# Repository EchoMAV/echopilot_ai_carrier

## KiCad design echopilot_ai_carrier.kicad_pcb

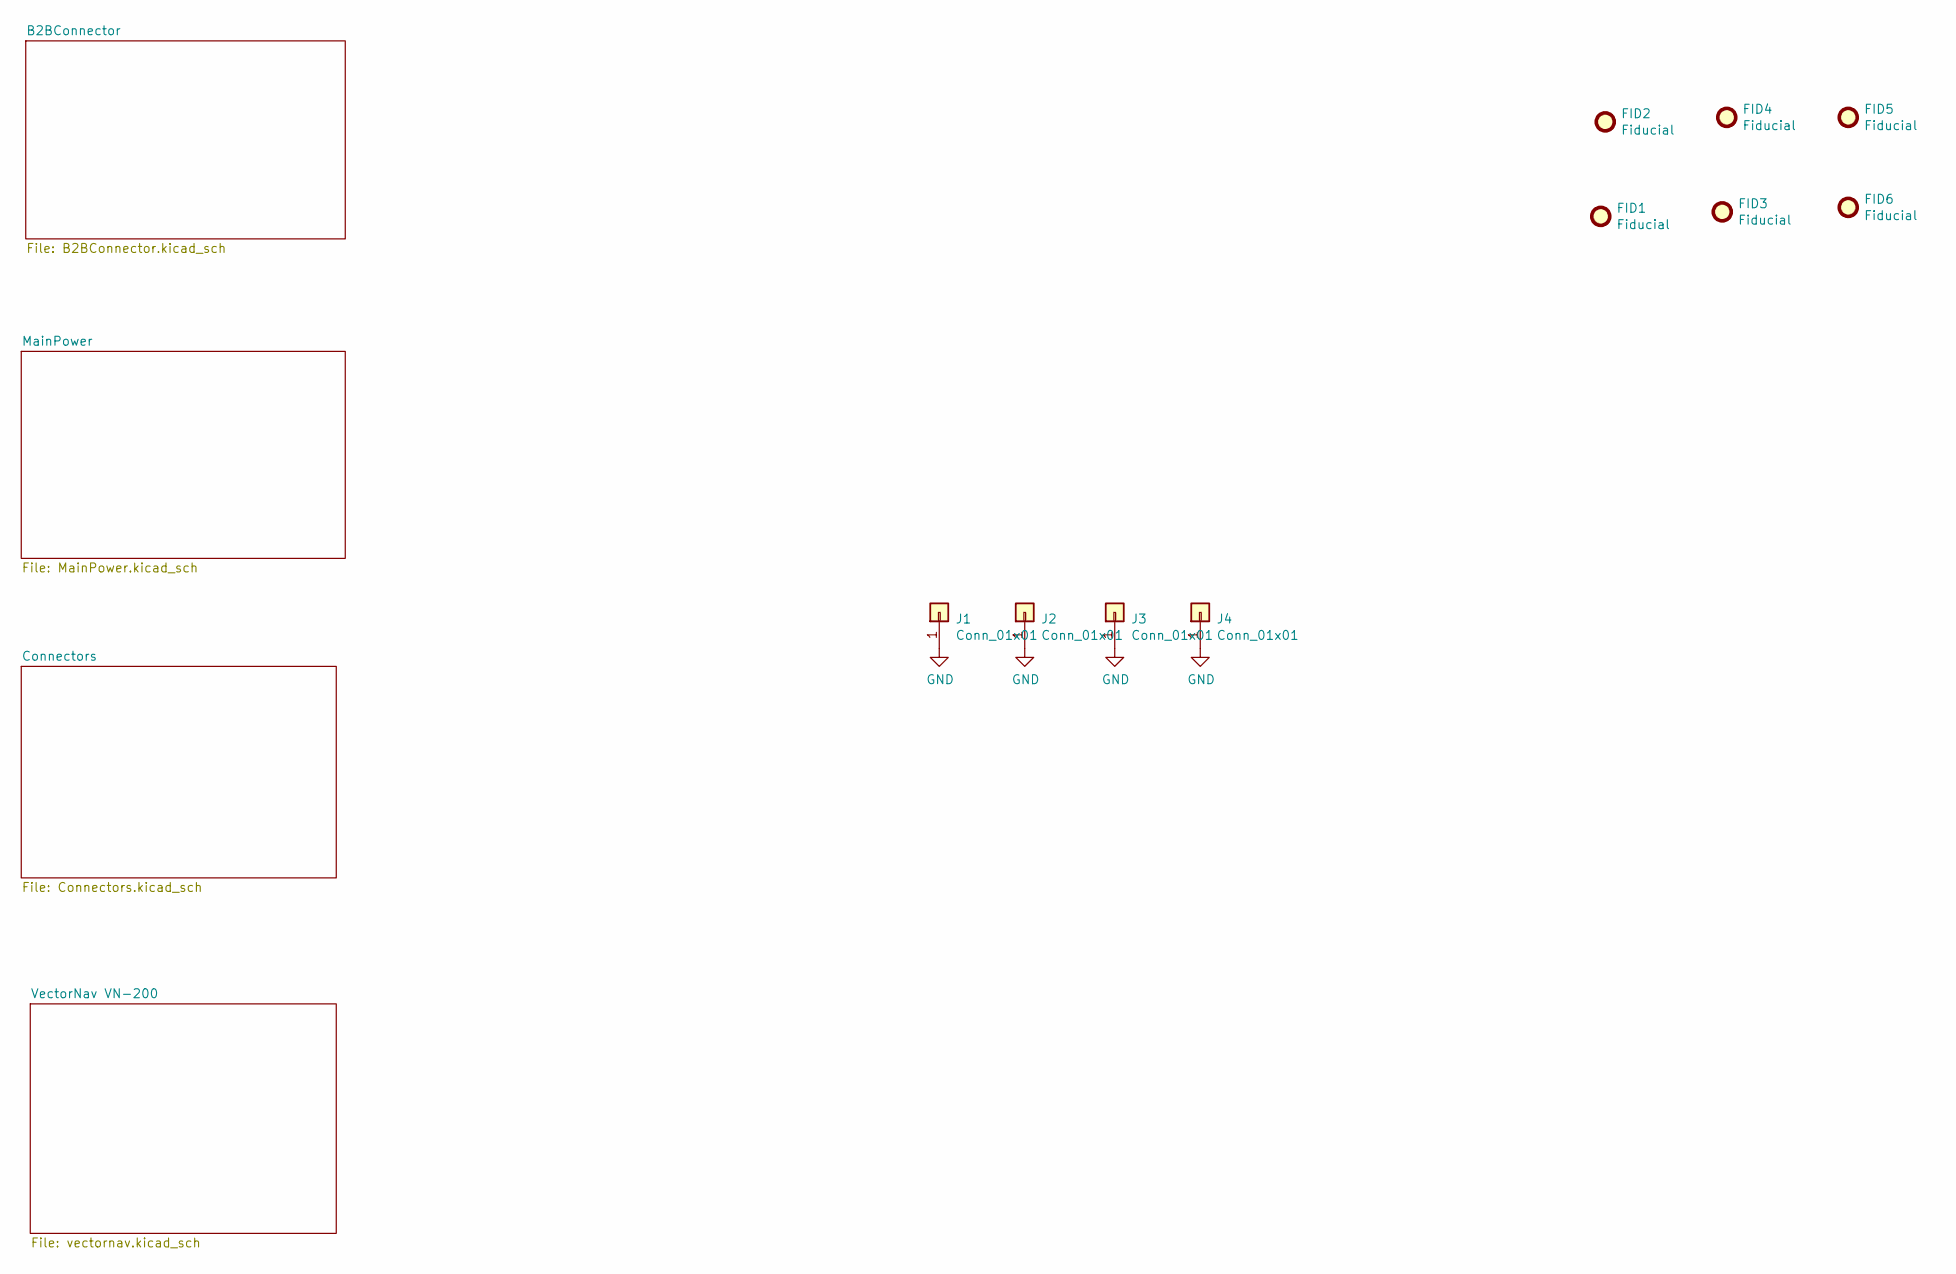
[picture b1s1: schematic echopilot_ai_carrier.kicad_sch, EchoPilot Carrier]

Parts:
FID1, FID2, FID3, FID4, FID5, FID6: Fiducial; Fiducial_0.5mm_Dia_1mm_Outer; Part Num DNI
J1, J2, J3, J4: Conn_01x01; MountingHole_2.7mm_M2.5_Pad_Via; Part Num DNI

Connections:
GND: J1.1, J2.1, J3.1, J4.1; also elsewhere on the board

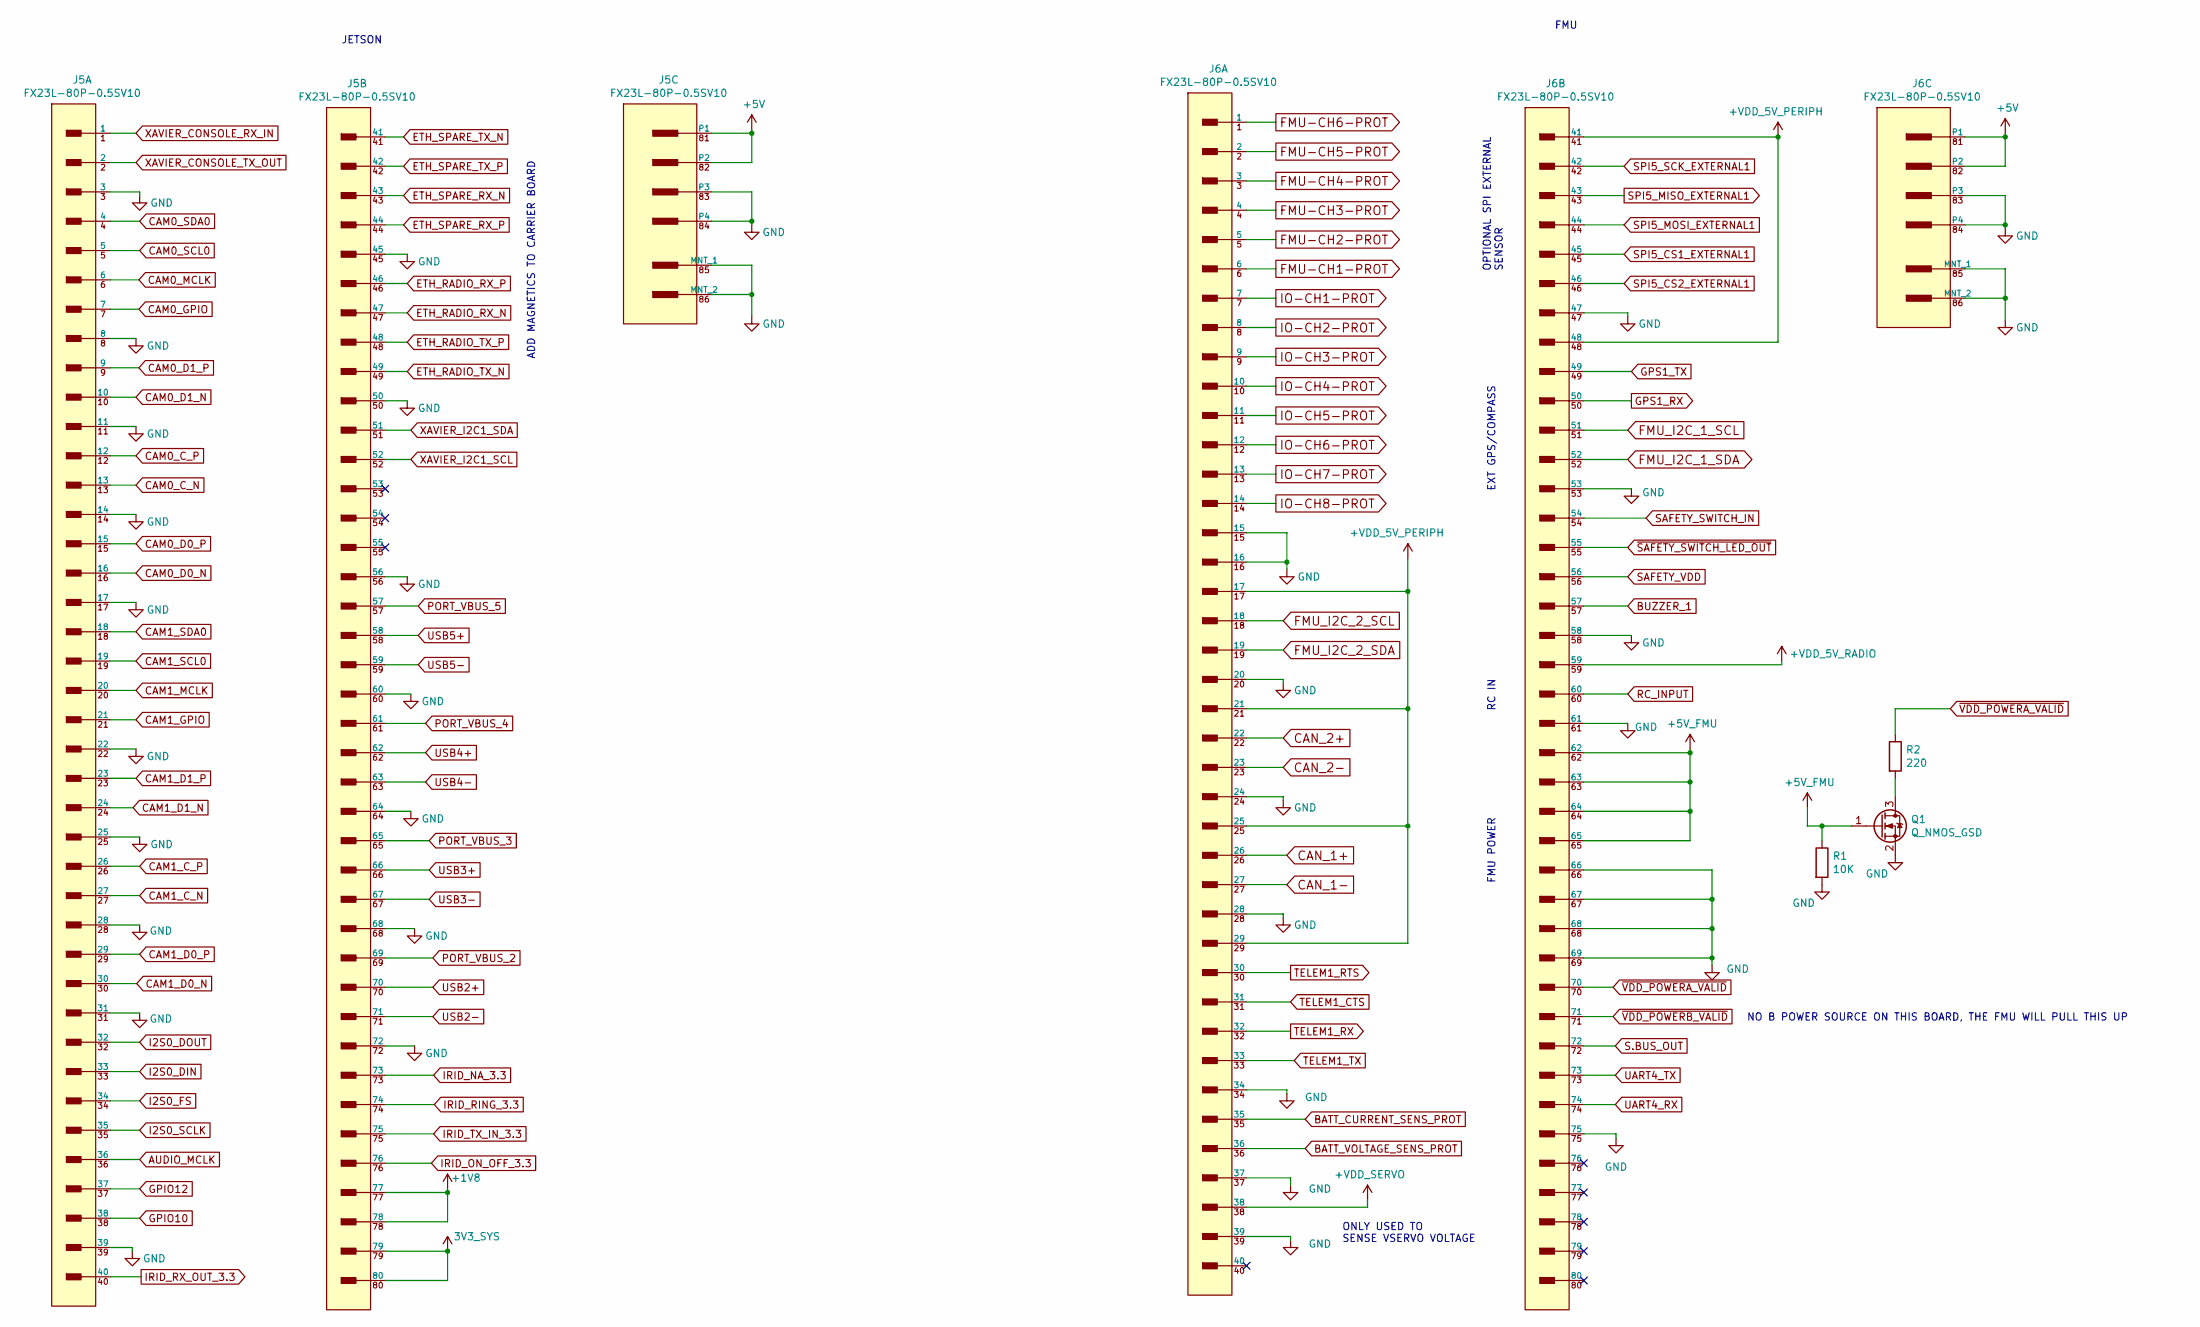
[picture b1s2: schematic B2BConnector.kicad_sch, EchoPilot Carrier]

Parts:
J5: FX23L-80P-0.5SV10; Hirose-FX23L-80P-0.5SV8-MFG; current rating 0.5/3A; voltage rating 50/200V; mouser part number 798-FX23L-80P-0.5SV8; digikey description CONN HDR
J6: FX23L-80P-0.5SV10; Hirose-FX23L-80P-0.5SV8-MFG; current rating 0.5/3A; voltage rating 50/200V; mouser part number FX23L-80P-0.5SV10; digikey description CONN HDR
Q1: Q_NMOS_GSD; SOT-23; Part Num BSS214NH6327XTSA1
R1: 10K; R_0201_0603Metric; Part Num ERJ-1GNF1002C
R2: 220; R_0201_0603Metric; Part Num ERJ-1GNF2200C

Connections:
3V3_SYS: J5.79, J5.80; also elsewhere on the board
+1V8: J5.77, J5.78
+5V_FMU: J6.62, J6.63, J6.64, J6.65, Q1.1 (G), R1.1; also elsewhere on the board
+VDD_5V_PERIPH: J6.17, J6.21, J6.25, J6.29, J6.41, J6.48; also elsewhere on the board
+VDD_5V_RADIO: J6.59; also elsewhere on the board
+VDD_SERVO: J6.38; also elsewhere on the board
AUDIO_MCLK: J5.36
BATT_CURRENT_SENS_PROT: J6.35; also elsewhere on the board
BATT_VOLTAGE_SENS_PROT: J6.36; also elsewhere on the board
BUZZER_1: J6.57; also elsewhere on the board
CAM0_C_N: J5.13; also elsewhere on the board
CAM0_C_P: J5.12; also elsewhere on the board
CAM0_D0_N: J5.16; also elsewhere on the board
CAM0_D0_P: J5.15; also elsewhere on the board
CAM0_D1_N: J5.10; also elsewhere on the board
CAM0_D1_P: J5.9; also elsewhere on the board
CAM0_GPIO: J5.7; also elsewhere on the board
CAM0_MCLK: J5.6; also elsewhere on the board
CAM0_SCL0: J5.5; also elsewhere on the board
CAM0_SDA0: J5.4; also elsewhere on the board
CAM1_C_N: J5.27; also elsewhere on the board
CAM1_C_P: J5.26; also elsewhere on the board
CAM1_D0_N: J5.30; also elsewhere on the board
CAM1_D0_P: J5.29; also elsewhere on the board
CAM1_D1_N: J5.24; also elsewhere on the board
CAM1_D1_P: J5.23; also elsewhere on the board
CAM1_GPIO: J5.21; also elsewhere on the board
CAM1_MCLK: J5.20; also elsewhere on the board
CAM1_SCL0: J5.19; also elsewhere on the board
CAM1_SDA0: J5.18; also elsewhere on the board
CAN_1+: J6.26; also elsewhere on the board
CAN_1-: J6.27; also elsewhere on the board
CAN_2+: J6.22; also elsewhere on the board
CAN_2-: J6.23; also elsewhere on the board
ETH_RADIO_RX_N: J5.47; also elsewhere on the board
ETH_RADIO_RX_P: J5.46; also elsewhere on the board
ETH_RADIO_TX_N: J5.49; also elsewhere on the board
ETH_RADIO_TX_P: J5.48; also elsewhere on the board
ETH_SPARE_RX_N: J5.43; also elsewhere on the board
ETH_SPARE_RX_P: J5.44; also elsewhere on the board
ETH_SPARE_TX_N: J5.41; also elsewhere on the board
ETH_SPARE_TX_P: J5.42; also elsewhere on the board
FMU-CH1-PROT: J6.6; also elsewhere on the board
FMU-CH2-PROT: J6.5; also elsewhere on the board
FMU-CH3-PROT: J6.4; also elsewhere on the board
FMU-CH4-PROT: J6.3; also elsewhere on the board
FMU-CH5-PROT: J6.2
FMU-CH6-PROT: J6.1
FMU_I2C_1_SCL: J6.51; also elsewhere on the board
FMU_I2C_1_SDA: J6.52; also elsewhere on the board
FMU_I2C_2_SCL: J6.18; also elsewhere on the board
FMU_I2C_2_SDA: J6.19; also elsewhere on the board
GND: J5.3, J5.8, J5.11, J5.14, J5.17, J5.22, J5.25, J5.28, J5.31, J5.39, J5.45, J5.50, J5.56, J5.60, J5.64, J5.68, J5.72, J5.83 (P3), J5.84 (P4), J5.85 (MNT_1), J5.86 (MNT_2), J6.15, J6.16, J6.20, J6.24, J6.28, J6.34, J6.37, J6.39, J6.47, J6.53, J6.58, J6.61, J6.66, J6.67, J6.68, J6.69, J6.75, J6.83 (P3), J6.84 (P4), J6.85 (MNT_1), J6.86 (MNT_2), Q1.2 (S), R1.2; also elsewhere on the board
GPIO10: J5.38
GPIO12: J5.37
GPS1_RX: J6.50; also elsewhere on the board
GPS1_TX: J6.49; also elsewhere on the board
I2S0_DIN: J5.33
I2S0_DOUT: J5.32
I2S0_FS: J5.34
I2S0_SCLK: J5.35
IO-CH1-PROT: J6.7; also elsewhere on the board
IO-CH2-PROT: J6.8; also elsewhere on the board
IO-CH3-PROT: J6.9; also elsewhere on the board
IO-CH4-PROT: J6.10; also elsewhere on the board
IO-CH5-PROT: J6.11; also elsewhere on the board
IO-CH6-PROT: J6.12; also elsewhere on the board
IO-CH7-PROT: J6.13; also elsewhere on the board
IO-CH8-PROT: J6.14; also elsewhere on the board
IRID_NA_3.3: J5.73; also elsewhere on the board
IRID_ON_OFF_3.3: J5.76; also elsewhere on the board
IRID_RING_3.3: J5.74; also elsewhere on the board
IRID_RX_OUT_3.3: J5.40; also elsewhere on the board
IRID_TX_IN_3.3: J5.75; also elsewhere on the board
unnamed: Q1.3 (D), R2.2
PORT_VBUS_2: J5.69; also elsewhere on the board
PORT_VBUS_3: J5.65; also elsewhere on the board
PORT_VBUS_4: J5.61; also elsewhere on the board
PORT_VBUS_5: J5.57; also elsewhere on the board
RC_INPUT: J6.60; also elsewhere on the board
S.BUS_OUT: J6.72; also elsewhere on the board
SAFETY_SWITCH_IN: J6.54; also elsewhere on the board
SAFETY_VDD: J6.56; also elsewhere on the board
SPI5_CS1_EXTERNAL1: J6.45
SPI5_CS2_EXTERNAL1: J6.46
SPI5_MISO_EXTERNAL1: J6.43
SPI5_MOSI_EXTERNAL1: J6.44
SPI5_SCK_EXTERNAL1: J6.42
TELEM1_CTS: J6.31; also elsewhere on the board
TELEM1_RTS: J6.30; also elsewhere on the board
TELEM1_RX: J6.32; also elsewhere on the board
TELEM1_TX: J6.33; also elsewhere on the board
UART4_RX: J6.74; also elsewhere on the board
UART4_TX: J6.73; also elsewhere on the board
USB2+: J5.70; also elsewhere on the board
USB2-: J5.71; also elsewhere on the board
USB3+: J5.66; also elsewhere on the board
USB3-: J5.67; also elsewhere on the board
USB4+: J5.62; also elsewhere on the board
USB4-: J5.63; also elsewhere on the board
USB5+: J5.58; also elsewhere on the board
USB5-: J5.59; also elsewhere on the board
XAVIER_CONSOLE_RX_IN: J5.1; also elsewhere on the board
XAVIER_CONSOLE_TX_OUT: J5.2; also elsewhere on the board
XAVIER_I2C1_SCL: J5.52
XAVIER_I2C1_SDA: J5.51
~SAFETY_SWITCH_LED_OUT: J6.55; also elsewhere on the board
~VDD_POWERA_VALID: J6.70, R2.1
~VDD_POWERB_VALID: J6.71

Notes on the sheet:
ADD MAGNETICS TO CARRIER BOARD
OPTIONAL SPI EXTERNAL SENSOR
RC IN
NO B POWER SOURCE ON THIS BOARD, THE FMU WILL PULL THIS UP
FMU
FMU POWER
ONLY USED TO SENSE VSERVO VOLTAGE
JETSON
EXT GPS/COMPASS

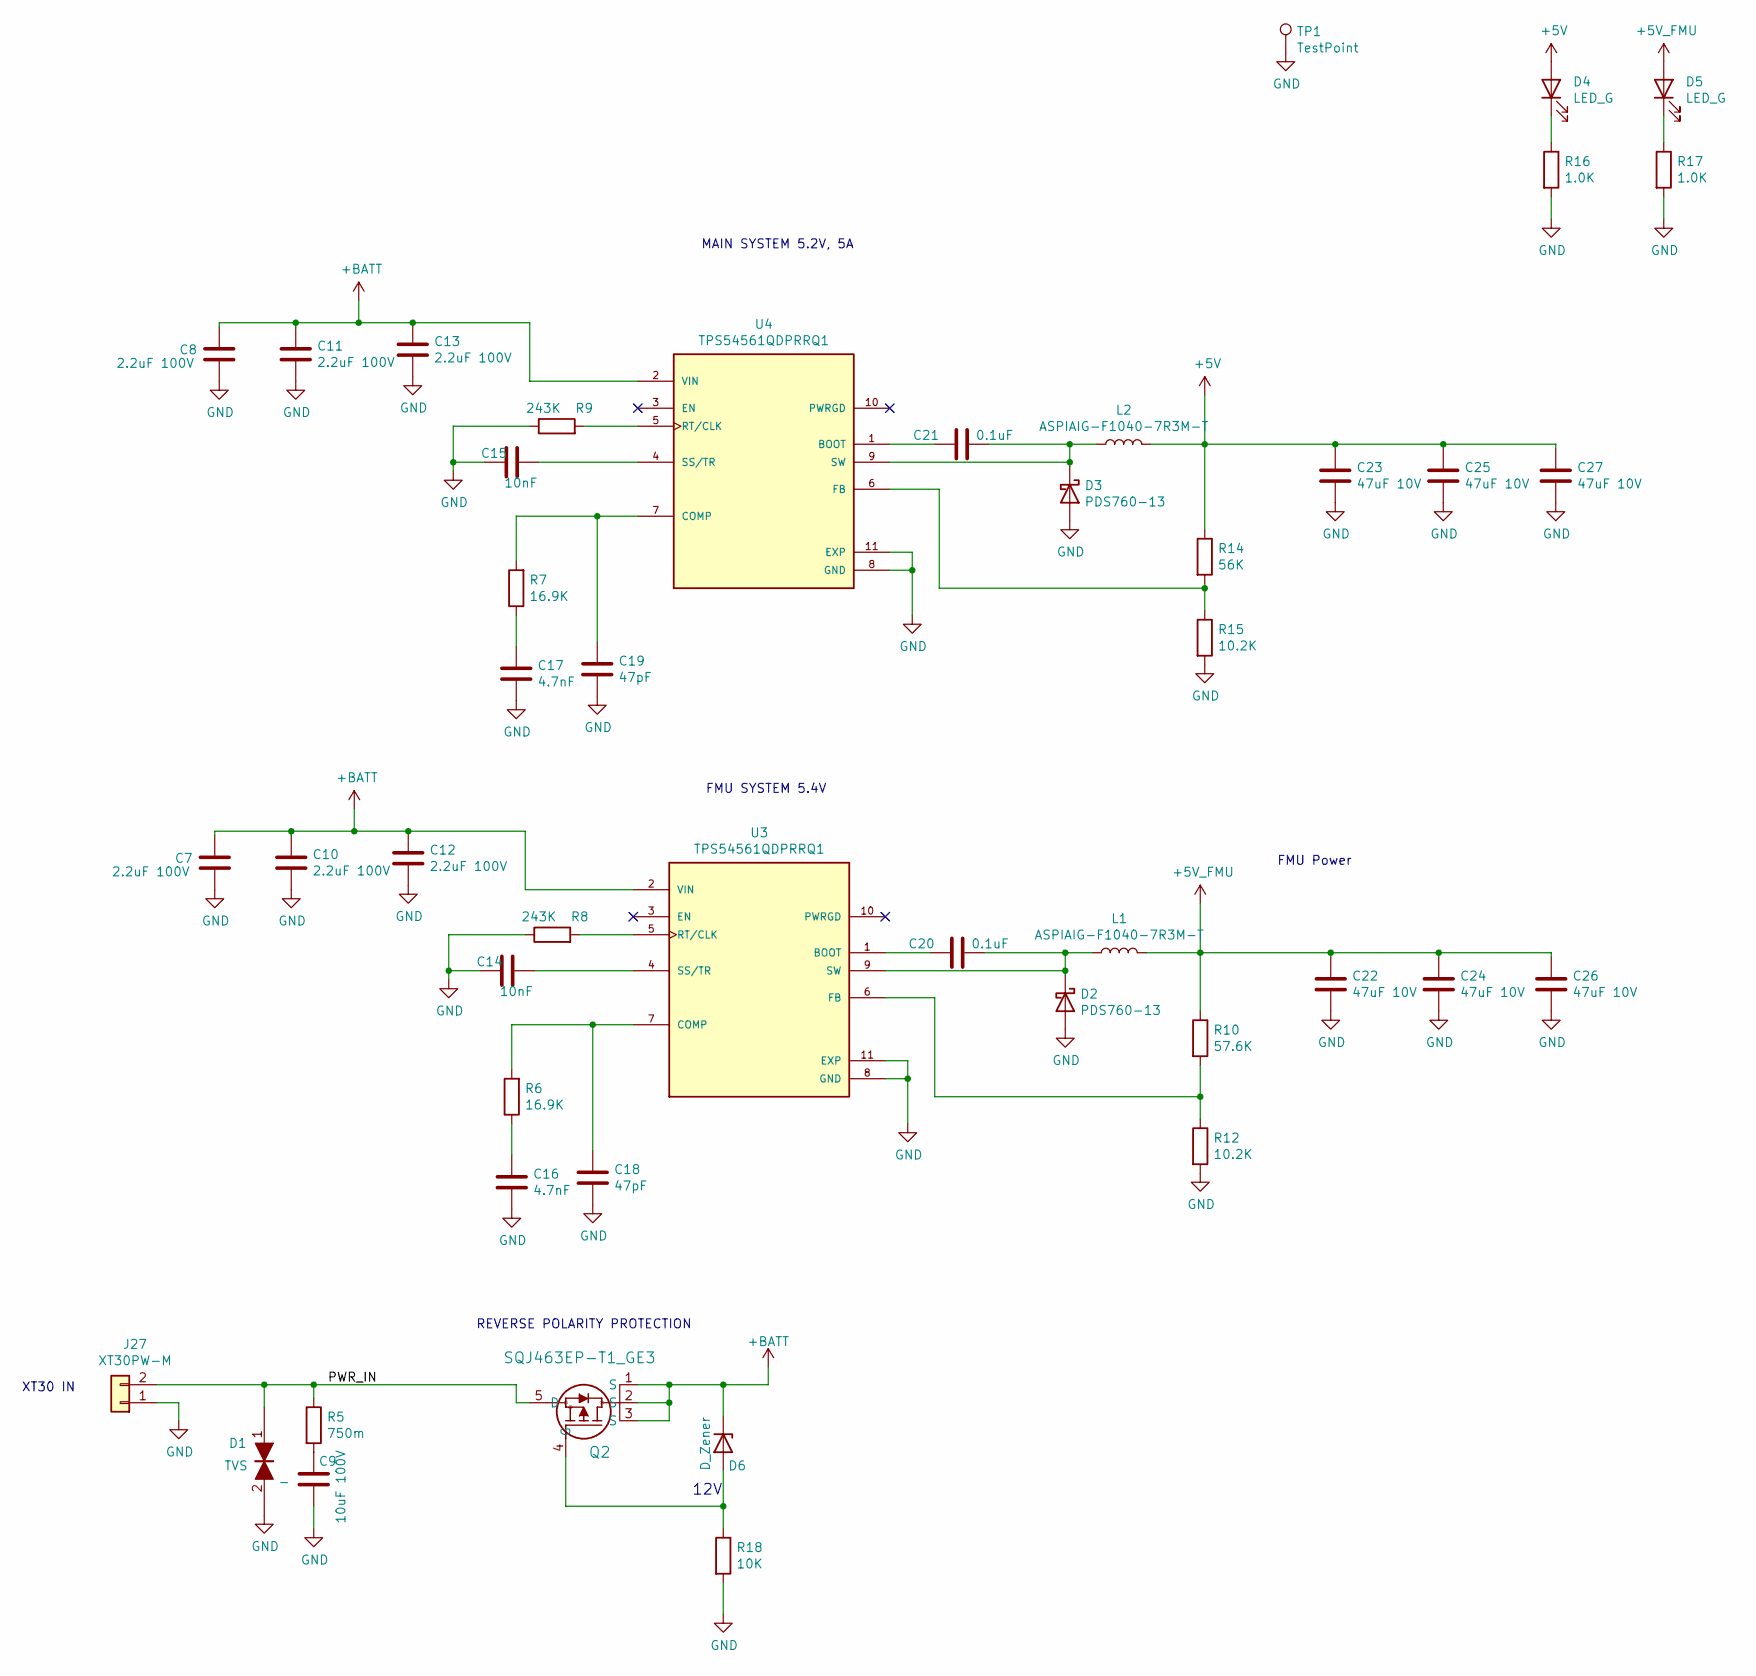
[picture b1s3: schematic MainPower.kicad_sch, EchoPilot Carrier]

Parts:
C7, C8, C10, C11, C12, C13: 2.2uF 100V; C_1206; Part Num 12061C225KAT2A
C9: 10uF 100V; C_1210; Part Num GRM32EC72A106KE05L
C14, C15: 10nF; C_0201; Part Num GRM033R71E103KE14D
C16, C17: 4.7nF; C_0201; Part Num GRM033R61E472KA12D
C18, C19: 47pF; C_0402; Part Num C0402C470J3RACAUTO
C20, C21: 0.1uF; C_0201; Part Num GRM033R61E104KE14J
C22, C23, C24, C25, C26, C27: 47uF 10V; C_1206; Part Num CL31A476MPHNNNE
D1: TVS; D_SOD-123F; Voltage _; Tolerance _; Part Num ATV02W101B-HF
D2, D3: PDS760-13; Part Num PDS760-13
D4, D5: LED_G; LED_0603; Part Num 150060VS75000
D6: D_Zener; D_SOD-523; Part Num MM5Z12VT1G
J27: XT30PW-M; AMASS_XT30PW-M_1x02_P2.50mm_Horizontal; Part Num XT30PW-M
L1, L2: ASPIAIG-F1040-7R3M-T; Part Num ASPIAIG-F1040-7R3M-T
Q2: SQJ463EP-T1_GE3; TO_63EP-T1_GE3_VIS; Part Num SQJ463EP-T1_GE3
R5: 750m; R_0402; Part Num ERJ-2BQJR75X
R6, R7: 16.9K; R_0201_0603Metric; Part Num ERJ-1GNF1692C
R8, R9: 243K; R_0201_0603Metric; Part Num ERJ-1GNF2433C
R10: 57.6K; R_0201_0603Metric; Part Num RC0201FR-0757K6L
R12, R15: 10.2K; R_0201_0603Metric; Part Num ERJ-1GNF1022C
R14: 56K; R_0201_0603Metric; Part Num RC0201FR-0756KL
R16, R17: 1.0K; R_0201_0603Metric; Part Num ERJ-1GEF1001C
R18: 10K; R_0402; Part Num ERJ-PA2J103X
TP1: TestPoint; Test_Point_Keystone_5015_Micro-Minature; Part Num 5015
U3, U4: TPS54561QDPRRQ1; SON80P400X400X80-11N; PARTREV F

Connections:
+5V_FMU: C22.1, C24.1, C26.1, D5.2 (A), L1.2, R10.1; also elsewhere on the board
+BATT: C7.1, C8.1, C10.1, C11.1, C12.1, C13.1, D6.1 (K), Q2.1 (S), Q2.2 (S), Q2.3 (S), U3.2 (VIN), U4.2 (VIN); also elsewhere on the board
/MainPower/PWR_IN: D1.1, J27.2, Q2.5 (D), R5.1
GND: C7.2, C8.2, C9.2, C10.2, C11.2, C12.2, C13.2, C14.2, C15.2, C16.2, C17.2, C18.2, C19.2, C22.2, C23.2, C24.2, C25.2, C26.2, C27.2, D1.2, D2.2 (A), D3.2 (A), J27.1, R8.1, R9.1, R12.2, R15.2, R16.2, R17.2, R18.2, TP1.1, U3.8 (GND), U3.11 (EXP), U4.8 (GND), U4.11 (EXP); also elsewhere on the board
unnamed: C9.1, R5.2
unnamed: C14.1, U3.4 (SS/TR)
unnamed: C15.1, U4.4 (SS/TR)
unnamed: C16.1, R6.1
unnamed: C17.1, R7.1
unnamed: C18.1, R6.2, U3.7 (COMP)
unnamed: C19.1, R7.2, U4.7 (COMP)
unnamed: C20.1, D2.1 (K), L1.1, U3.9 (SW)
unnamed: C20.2, U3.1 (BOOT)
unnamed: C21.1, D3.1 (K), L2.1, U4.9 (SW)
unnamed: C21.2, U4.1 (BOOT)
unnamed: D4.1 (K), R16.1
unnamed: D5.1 (K), R17.1
unnamed: D6.2 (A), Q2.4 (G), R18.1
unnamed: R8.2, U3.5 (RT/CLK)
unnamed: R9.2, U4.5 (RT/CLK)
unnamed: R10.2, R12.1, U3.6 (FB)
unnamed: R14.2, R15.1, U4.6 (FB)

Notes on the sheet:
FMU SYSTEM 5.4V
REVERSE POLARITY PROTECTION
MAIN SYSTEM 5.2V, 5A
12V
XT30 IN
FMU Power

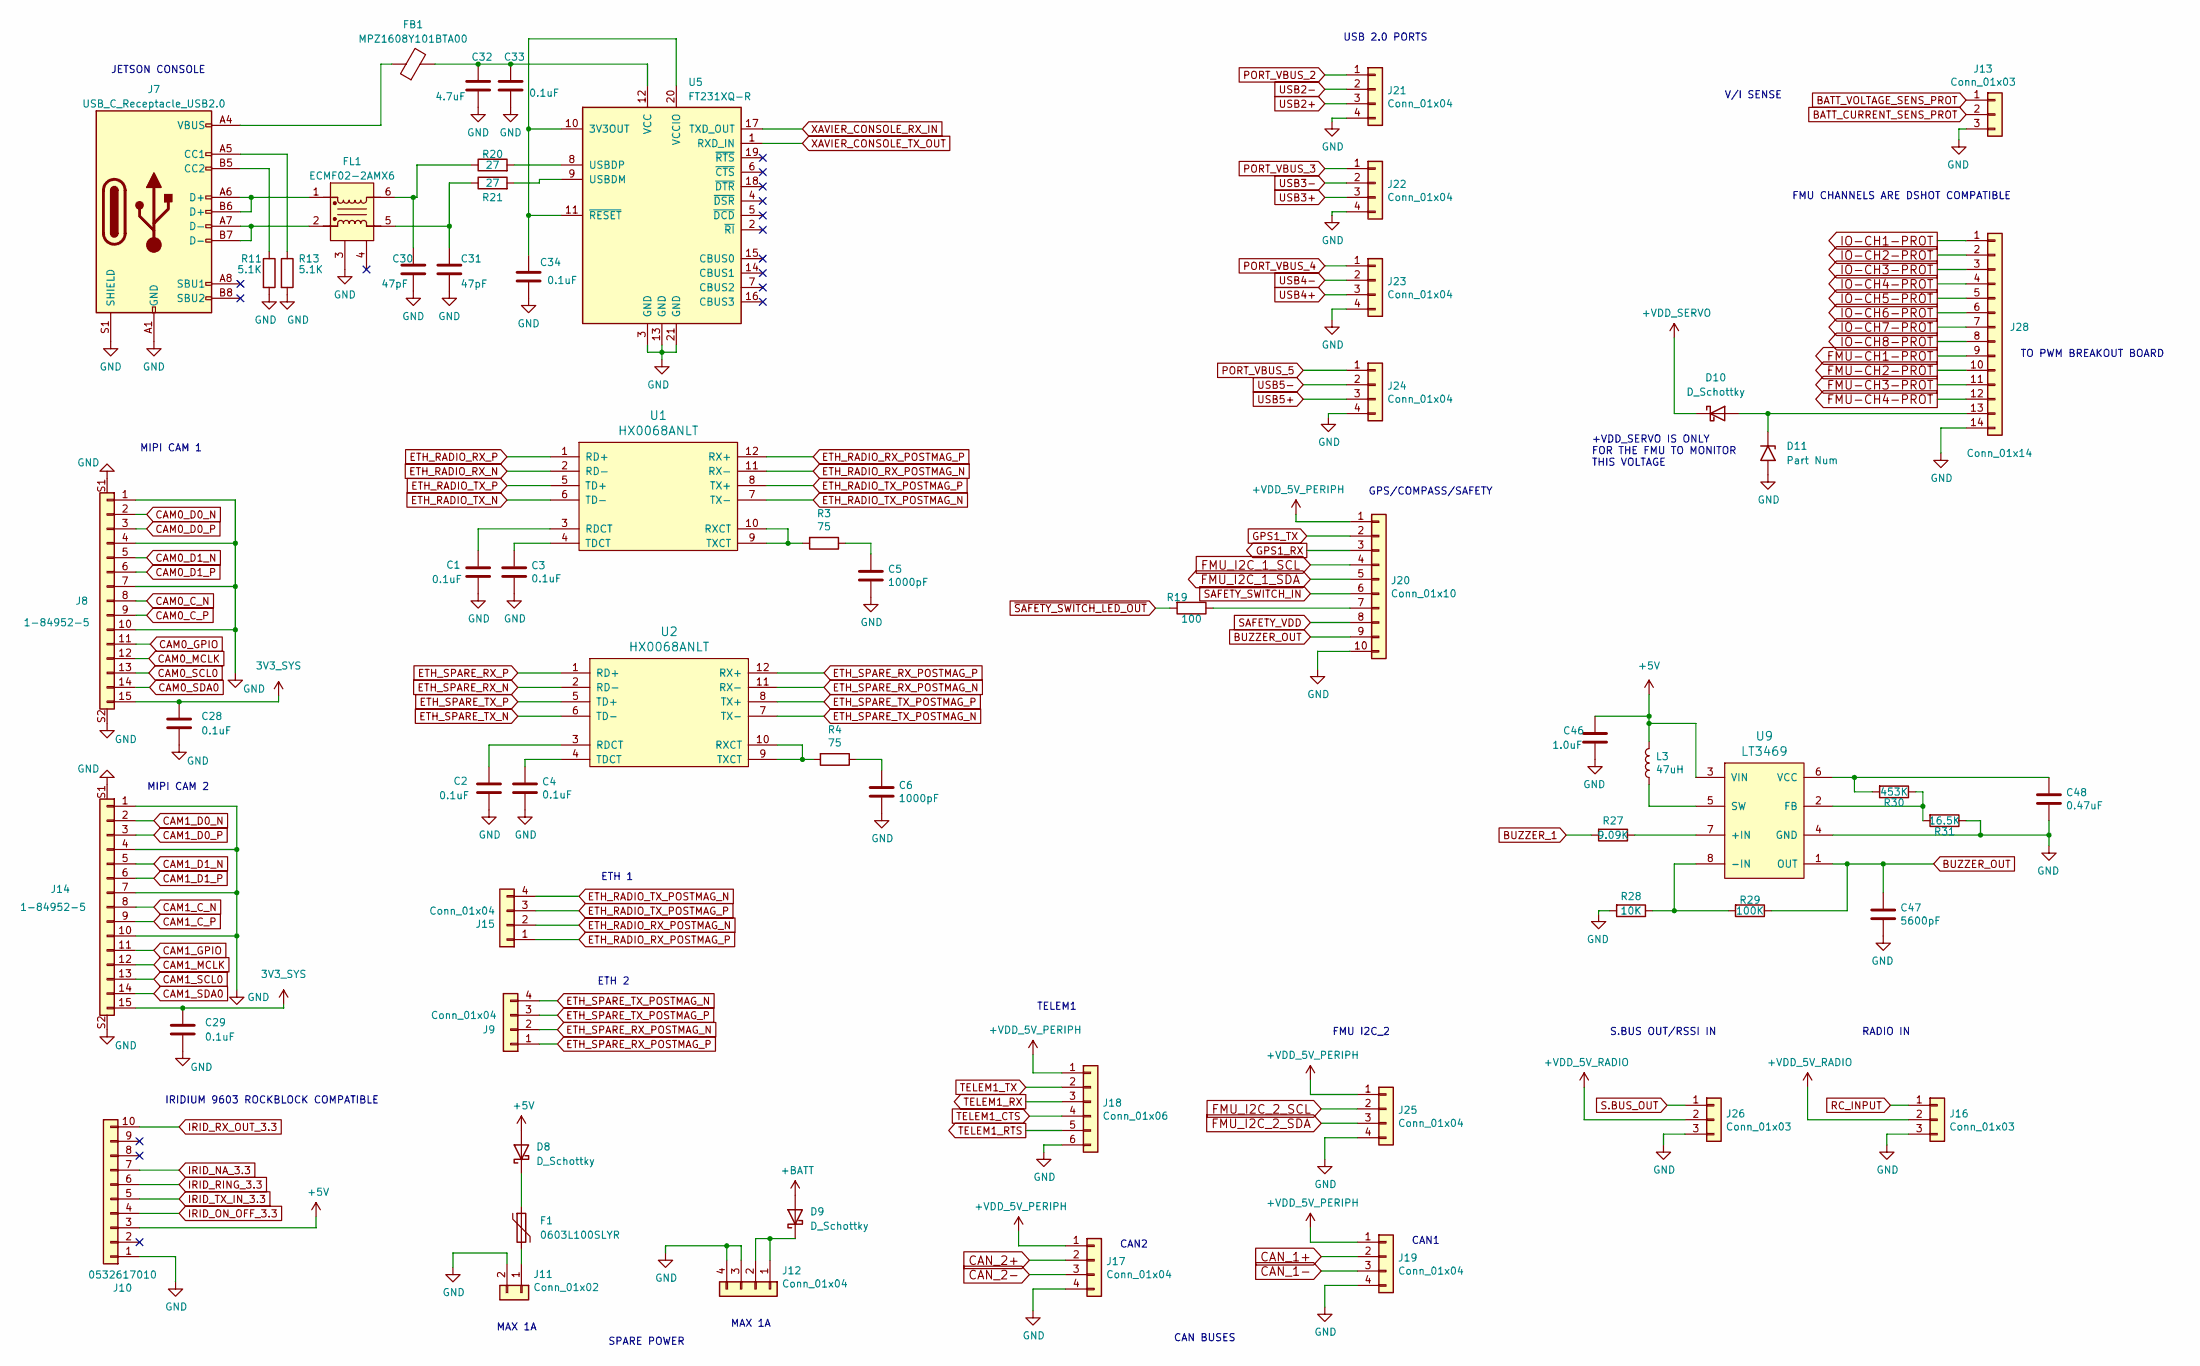
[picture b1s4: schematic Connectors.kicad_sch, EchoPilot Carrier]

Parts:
C1, C2, C3, C4: 0.1uF; C_0201; Part Num GRM033R61E104KE14J
C5, C6: 1000pF; C_0201; Part Num GRM033R71H102KA12D
C28, C29: 0.1uF; C_0201_0603Metric
C30, C31: 47pF; C_0201_0603Metric; Part Num 02013A470JAT2A
C32: 4.7uF; C_0805_2012Metric; Part Num CL21B475KOFNFNE
C33, C34: 0.1uF; C_0201_0603Metric; Part Num GRM033R61E104KE14J
C46: 1.0uF; C_0201_0603Metric; Part Num CL03A105MO3NRNH
C47: 5600pF; C_0201_0603Metric; Part Num GRM033R61E562KA12D
C48: 0.47uF; C_0201_0603Metric; Part Num EMK063BBJ474KPLF
D8, D9: D_Schottky; D_SMA; Part Num B340LA-13-F
D10: D_Schottky; D_0402_1005Metric; Part Num CDBQC0130L-HF
D11: Part Num; D_0402_1005Metric; Part Num PESD0402-140
F1: 0603L100SLYR; Fuse_0603_1608Metric; Part Num 0603L100SLYR
FB1: MPZ1608Y101BTA00; L_0603_1608Metric; Part Num MPZ1608Y101BTA00
FL1: ECMF02-2AMX6; QFN-6L_STM; Part Num ECMF02-2AMX6
J7: USB_C_Receptacle_USB2.0; USB_C_Receptacle_Amphenol_12401610E4-2A; Part Num 12401610E4#2A
J8, J14: 1-84952-5; TE_1-84952-5; Part Num 1-84952-5
J9, J15, J17, J19, J21, J22, J23, J24, J25: Conn_01x04; JST_GH_SM04B-GHS-TB_1x04-1MP_P1.25mm_Horizontal; Part Num SM04B-GHS-TB(LF)(SN)
J10: 0532617010; Molex_PicoBlade_53261-1071_10x1.25mm_Angled; Part Num 0532617010
J11: Conn_01x02; JST_GH_SM02B-GHS-TB_02x1.25mm_Angled; Part Num SM02B-GHS-TB(LF)(SN)
J12: Conn_01x04; JST_GH_SM04B-GHS-TB_04x1.25mm_Angled; Part Num SM04B-GHS-TB(LF)(SN)
J13, J26: Conn_01x03; JST_GH_SM03B-GHS-TB_1x03-1MP_P1.25mm_Horizontal; Part Num SM03B-GHS-TB(LF)(SN)
J16: Conn_01x03; JST_GH_SM03B-GHS-TB_03x1.25mm_Angled; Part Num SM03B-GHS-TB(LF)(SN)
J18: Conn_01x06; JST_GH_SM06B-GHS-TB_1x06-1MP_P1.25mm_Horizontal; Part Num SM06B-GHS-TB(LF)(SN)
J20: Conn_01x10; JST_GH_SM10B-GHS-TB_10x1.25mm_Angled; Part Num SM10B-GHS-TB(LF)(SN)
J28: Conn_01x14; JST_GH_SM14B-GHS-TB_1x14-1MP_P1.25mm_Horizontal; Part Num SM14B-GHS-TB(LF)(SN)-
L3: 47uH; IND_LQH32CN470K23L; Part Num LQH32CN470K23L
R3, R4: 75; R_0201_0603Metric; Part Num ERJ-1GNF75R0C
R11, R13: 5.1K; R_0201_0603Metric; Part Num ERJ-1GNJ512C
R19: 100; R_0201_0603Metric; Part Num ERJ-U01F1000C
R20, R21: 27; R_0201_0603Metric; Part Num ERJ-1GNJ270C
R27: 9.09K; R_0201_0603Metric; Part Num ERJ-1GNF9091C
R28: 10K; R_0201_0603Metric; Part Num ERJ-U01F1002C
R29: 100K; R_0201_0603Metric; Part Num ERJ-1GEF1003C
R30: 453K; R_0201_0603Metric; Part Num ERJ-1GNF4533C
R31: 16.5K; R_0201_0603Metric; Part Num ERJ-1GNF1652C
U1, U2: HX0068ANLT; HX0068ANLT_r2; Part Num HX0068ANLT
U5: FT231XQ-R; QFN20_FT231XQ_FTD; Part Num FT231XQ-R
U9: LT3469; SOT-23-8; Part Num LT3469ETS8#TRMPBF

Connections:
3V3_SYS: C28.1, C29.1, J8.15, J14.15; also elsewhere on the board
+BATT: D9.2 (A); also elsewhere on the board
+VDD_5V_PERIPH: J17.1, J18.1, J19.1, J20.1, J25.1; also elsewhere on the board
+VDD_5V_RADIO: J16.2, J26.2; also elsewhere on the board
+VDD_SERVO: D10.1 (K); also elsewhere on the board
BATT_CURRENT_SENS_PROT: J13.2; also elsewhere on the board
BATT_VOLTAGE_SENS_PROT: J13.1; also elsewhere on the board
BUZZER_1: R27.2; also elsewhere on the board
BUZZER_OUT: C47.1, J20.9, R29.1, U9.1 (OUT)
CAM0_C_N: J8.8; also elsewhere on the board
CAM0_C_P: J8.9; also elsewhere on the board
CAM0_D0_N: J8.2; also elsewhere on the board
CAM0_D0_P: J8.3; also elsewhere on the board
CAM0_D1_N: J8.5; also elsewhere on the board
CAM0_D1_P: J8.6; also elsewhere on the board
CAM0_GPIO: J8.11; also elsewhere on the board
CAM0_MCLK: J8.12; also elsewhere on the board
CAM0_SCL0: J8.13; also elsewhere on the board
CAM0_SDA0: J8.14; also elsewhere on the board
CAM1_C_N: J14.8; also elsewhere on the board
CAM1_C_P: J14.9; also elsewhere on the board
CAM1_D0_N: J14.2; also elsewhere on the board
CAM1_D0_P: J14.3; also elsewhere on the board
CAM1_D1_N: J14.5; also elsewhere on the board
CAM1_D1_P: J14.6; also elsewhere on the board
CAM1_GPIO: J14.11; also elsewhere on the board
CAM1_MCLK: J14.12; also elsewhere on the board
CAM1_SCL0: J14.13; also elsewhere on the board
CAM1_SDA0: J14.14; also elsewhere on the board
CAN_1+: J19.2; also elsewhere on the board
CAN_1-: J19.3; also elsewhere on the board
CAN_2+: J17.2; also elsewhere on the board
CAN_2-: J17.3; also elsewhere on the board
ETH_RADIO_RX_N: U1.2 (RD-); also elsewhere on the board
ETH_RADIO_RX_P: U1.1 (RD+); also elsewhere on the board
ETH_RADIO_RX_POSTMAG_N: J15.2, U1.11 (RX-)
ETH_RADIO_RX_POSTMAG_P: J15.1, U1.12 (RX+)
ETH_RADIO_TX_N: U1.6 (TD-); also elsewhere on the board
ETH_RADIO_TX_P: U1.5 (TD+); also elsewhere on the board
ETH_RADIO_TX_POSTMAG_N: J15.4, U1.7 (TX-)
ETH_RADIO_TX_POSTMAG_P: J15.3, U1.8 (TX+)
ETH_SPARE_RX_N: U2.2 (RD-); also elsewhere on the board
ETH_SPARE_RX_P: U2.1 (RD+); also elsewhere on the board
ETH_SPARE_RX_POSTMAG_N: J9.2, U2.11 (RX-)
ETH_SPARE_RX_POSTMAG_P: J9.1, U2.12 (RX+)
ETH_SPARE_TX_N: U2.6 (TD-); also elsewhere on the board
ETH_SPARE_TX_P: U2.5 (TD+); also elsewhere on the board
ETH_SPARE_TX_POSTMAG_N: J9.4, U2.7 (TX-)
ETH_SPARE_TX_POSTMAG_P: J9.3, U2.8 (TX+)
FMU-CH1-PROT: J28.9; also elsewhere on the board
FMU-CH2-PROT: J28.10; also elsewhere on the board
FMU-CH3-PROT: J28.11; also elsewhere on the board
FMU-CH4-PROT: J28.12; also elsewhere on the board
FMU_I2C_1_SCL: J20.4; also elsewhere on the board
FMU_I2C_1_SDA: J20.5; also elsewhere on the board
FMU_I2C_2_SCL: J25.2; also elsewhere on the board
FMU_I2C_2_SDA: J25.3; also elsewhere on the board
GND: C1.2, C2.2, C3.2, C4.2, C5.2, C6.2, C28.2, C29.2, C30.2, C31.2, C32.2, C33.2, C34.2, C46.2, C47.2, C48.2, D11.2 (A2), FL1.3 (GND), J7.A1 (GND), J7.A12 (GND), J7.B1 (GND), J7.B12 (GND), J7.S1 (SHIELD), J8.1, J8.4, J8.7, J8.10, J8.S1, J8.S2, J10.1, J11.2, J12.3, J12.4, J13.3, J14.1, J14.4, J14.7, J14.10, J14.S1, J14.S2, J16.3, J17.4, J18.6, J19.4, J20.10, J21.4, J22.4, J23.4, J24.4, J25.4, J26.3, J28.14, R11.2, R13.2, R28.2, R31.1, U5.3 (GND), U5.13 (GND), U5.21 (GND), U9.4 (GND); also elsewhere on the board
GPS1_RX: J20.3; also elsewhere on the board
GPS1_TX: J20.2; also elsewhere on the board
IO-CH1-PROT: J28.1; also elsewhere on the board
IO-CH2-PROT: J28.2; also elsewhere on the board
IO-CH3-PROT: J28.3; also elsewhere on the board
IO-CH4-PROT: J28.4; also elsewhere on the board
IO-CH5-PROT: J28.5; also elsewhere on the board
IO-CH6-PROT: J28.6; also elsewhere on the board
IO-CH7-PROT: J28.7; also elsewhere on the board
IO-CH8-PROT: J28.8; also elsewhere on the board
IRID_NA_3.3: J10.7; also elsewhere on the board
IRID_ON_OFF_3.3: J10.4; also elsewhere on the board
IRID_RING_3.3: J10.6; also elsewhere on the board
IRID_RX_OUT_3.3: J10.10; also elsewhere on the board
IRID_TX_IN_3.3: J10.5; also elsewhere on the board
unnamed: C1.1, U1.3 (RDCT)
unnamed: C2.1, U2.3 (RDCT)
unnamed: C3.1, U1.4 (TDCT)
unnamed: C4.1, U2.4 (TDCT)
unnamed: C5.1, R3.1
unnamed: C6.1, R4.1
unnamed: C30.1, FL1.6 (D+_OUT), R20.1
unnamed: C31.1, FL1.5 (D-_OUT), R21.1
unnamed: C32.1, C33.1, FB1.2, U5.12 (VCC)
unnamed: C34.1, U5.10 (3V3OUT), U5.11 (~RESET), U5.20 (VCCIO)
unnamed: C48.1, R30.2, U9.6 (VCC)
unnamed: D8.1 (K), F1.1
unnamed: D9.1 (K), J12.1, J12.2
unnamed: D10.2 (A), D11.1 (A1), J28.13
unnamed: F1.2, J11.1
unnamed: FB1.1, J7.A4 (VBUS), J7.A9 (VBUS), J7.B4 (VBUS), J7.B9 (VBUS)
unnamed: FL1.1 (D+_IN), J7.A6 (D+), J7.B6 (D+)
unnamed: FL1.2 (D-_IN), J7.A7 (D-), J7.B7 (D-)
unnamed: J7.A5 (CC1), R13.1
unnamed: J7.B5 (CC2), R11.1
unnamed: J20.7, R19.1
unnamed: L3.1, U9.5 (SW)
unnamed: R3.2, U1.9 (TXCT), U1.10 (RXCT)
unnamed: R4.2, U2.9 (TXCT), U2.10 (RXCT)
unnamed: R20.2, U5.8 (USBDP)
unnamed: R21.2, U5.9 (USBDM)
unnamed: R27.1, U9.7 (+IN)
unnamed: R28.1, R29.2, U9.8 (-IN)
unnamed: R30.1, R31.2, U9.2 (FB)
PORT_VBUS_2: J21.1; also elsewhere on the board
PORT_VBUS_3: J22.1; also elsewhere on the board
PORT_VBUS_4: J23.1; also elsewhere on the board
PORT_VBUS_5: J24.1; also elsewhere on the board
RC_INPUT: J16.1; also elsewhere on the board
S.BUS_OUT: J26.1; also elsewhere on the board
SAFETY_SWITCH_IN: J20.6; also elsewhere on the board
SAFETY_VDD: J20.8; also elsewhere on the board
TELEM1_CTS: J18.4; also elsewhere on the board
TELEM1_RTS: J18.5; also elsewhere on the board
TELEM1_RX: J18.3; also elsewhere on the board
TELEM1_TX: J18.2; also elsewhere on the board
USB2+: J21.3; also elsewhere on the board
USB2-: J21.2; also elsewhere on the board
USB3+: J22.3; also elsewhere on the board
USB3-: J22.2; also elsewhere on the board
USB4+: J23.3; also elsewhere on the board
USB4-: J23.2; also elsewhere on the board
USB5+: J24.3; also elsewhere on the board
USB5-: J24.2; also elsewhere on the board
XAVIER_CONSOLE_RX_IN: U5.17 (TXD_OUT); also elsewhere on the board
XAVIER_CONSOLE_TX_OUT: U5.1 (RXD_IN); also elsewhere on the board
~SAFETY_SWITCH_LED_OUT: R19.2; also elsewhere on the board

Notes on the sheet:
MIPI CAM 1
IRIDIUM 9603 ROCKBLOCK COMPATIBLE
V/I SENSE
JETSON CONSOLE
+VDD_SERVO IS ONLY FOR THE FMU TO MONITOR THIS VOLTAGE
ETH 1
GPS/COMPASS/SAFETY
TELEM1
CAN1
SPARE POWER
MAX 1A
S.BUS OUT/RSSI IN
CAN BUSES
USB 2.0 PORTS
MIPI CAM 2
FMU I2C_2
ETH 2
RADIO IN
FMU CHANNELS ARE DSHOT COMPATIBLE
CAN2
TO PWM BREAKOUT BOARD
